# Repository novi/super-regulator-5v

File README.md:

# super-regulator-5v
Opamp-based super regulator (5V) schematic and PCB(KiCad format).

Negative voltage version is [here](https://github.com/novi/super-regulator-5v/tree/negative-voltage-version).

## Suitable parts

* TBD

## Acknowledgments

* [Op-Amp Based Linear Regulators](https://tangentsoft.net/elec/opamp-linreg.html)
* [The Superregs](https://linearaudio.nl/superregs)

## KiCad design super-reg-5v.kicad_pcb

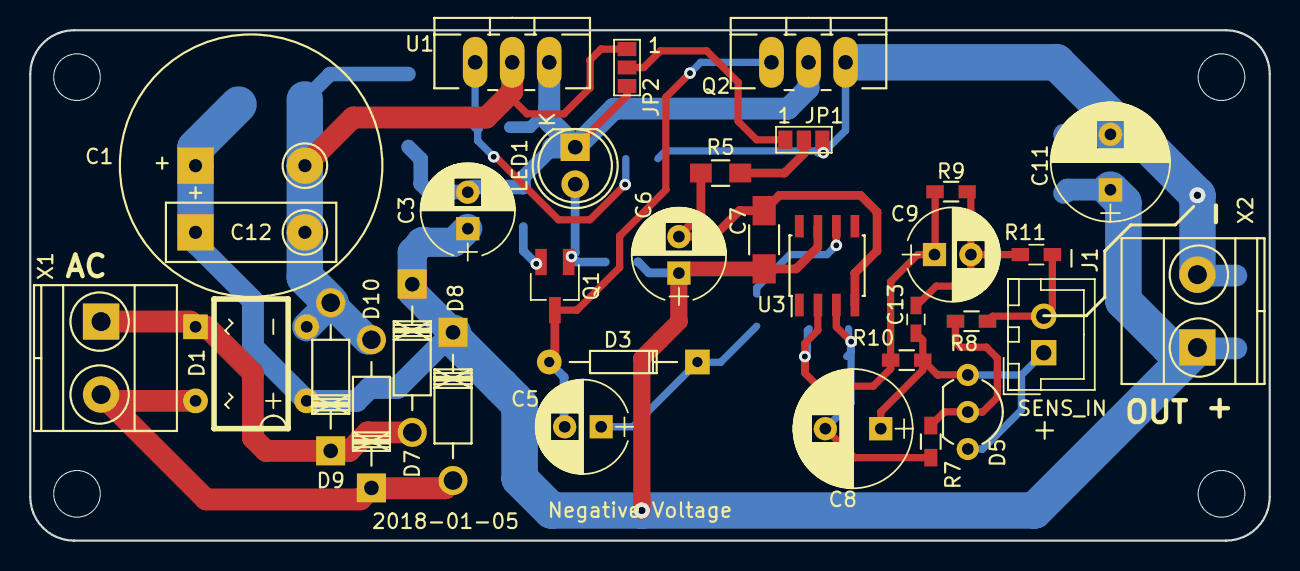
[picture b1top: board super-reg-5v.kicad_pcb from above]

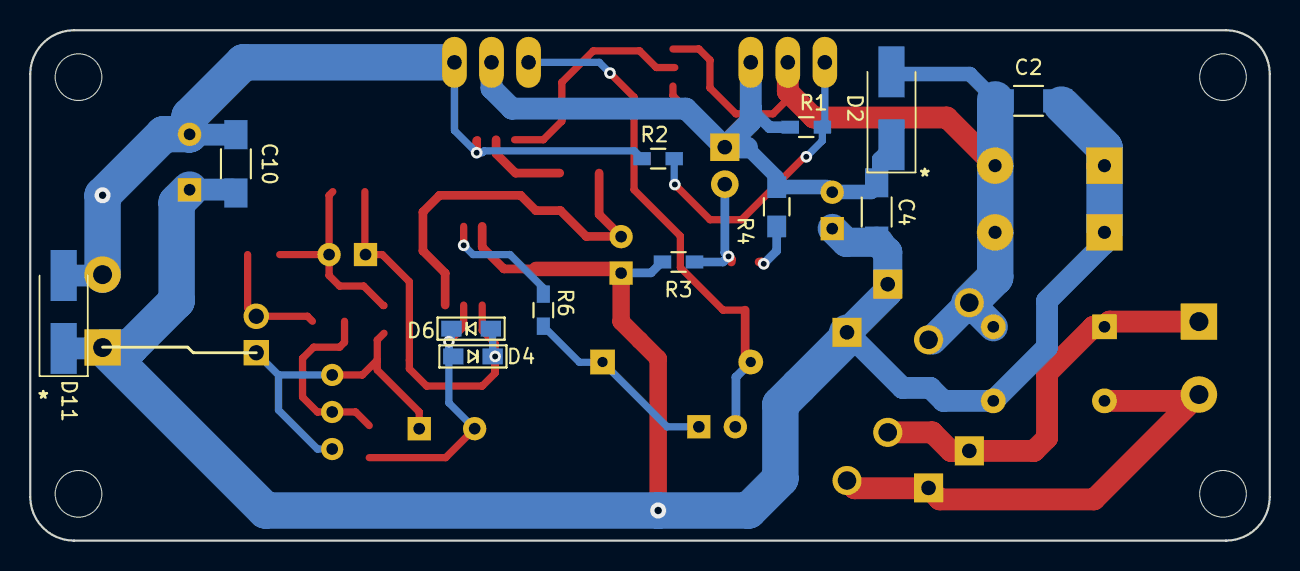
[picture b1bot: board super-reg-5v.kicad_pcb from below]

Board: 2 copper layers, 85.0 x 35.0 mm, 45 parts (12 on the bottom side), 21 nets.

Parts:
C1: 2200u; C_Radial_D18_L36_P7.5_LargePad
C2, C4, C7, C10: 0.1u C0G; C_1206_HandSoldering
C3, C6: 100u 35v LowESR; CP_Radial_D6.3mm_P2.50mm
C5: 100u LowESR; CP_Radial_D6.3mm_P2.50mm
C8: 100u EP-Cap; CP_Radial_D8.0mm_P3.80mm
C9: 100u; CP_Radial_D6.3mm_P2.50mm
C11: 220u OS-CON; CP_Radial_D8.0mm_P3.80mm
C12: C1-Alt; C_Radial_D18_L36_P7.5_LargePad_NoCircle
C13: 100p; C_0603_HandSoldering
D1: DB-1S(SDI2100); DB-1_DIP
D2, D11: D; D_SMA_Handsoldering
D3: ZD 2.7V; Diode_DO-35_SOD27_Horizontal_RM10
D4, D6: D; UMD2-handsoldering
D5: TL431LP; TO-92_Inline_Wide
D7, D8, D9, D10: PWR_D; Diode_DO-41_SOD81_Horizontal_RM10
J1: SENS_IN; JST_XH_B02B-XH-A_02x2.50mm_Straight
JP1: OPAMP_PWR_2; GS3
JP2: OPAMP_PWR_1; GS3
LED1: LED GREEN(2V); LED-5MM
Q1: 2SC2712GR; SC-59_Handsoldering
Q2: D45H11; TO-220_Neutral123_Vertical_LargePads
R1, R9, R10: 1k 1%; R_0603_HandSoldering
R2: 820 1%; R_0603_HandSoldering
R3: 10k; R_0603_HandSoldering
R4: 240; R_0805_HandSoldering
R5: 100; R_0805_HandSoldering
R6: 10; R_0603_HandSoldering
R7: 470; R_0603_HandSoldering
R8: 2.2k; R_0603_HandSoldering
R11: 100; R_0603_HandSoldering
U1: LM337T; TO-220_Neutral123_Vertical_LargePads
U3: AD825; SOIC-8_3.9x4.9mm_Pitch1.27mm
X1: AC_IN; TerminalBlock_Pheonix_MKDS1.5-2pol
X2: DC_OUT; TerminalBlock_Pheonix_MKDS1.5-2pol

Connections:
/OPAMP_N: C9.1, D4.1, D6.2, R9.2, R10.1, U3.2
unnamed: C1.1, C2.2, C3.1, C4.2, C6.1, C7.2, C10.2, C11.1, C12.1, D1.3, D7.1, D8.1, D11.1, R3.2, U3.7, X2.1
unnamed: C1.2, C2.1, C12.2, D1.4, D2.2, D9.2, D10.2, JP2.1, U1.2
unnamed: C3.2, C4.1, D2.1, JP2.3, LED1.1, Q2.2, R1.1, R4.1, U1.3
unnamed: C5.1, D3.1, R6.2
unnamed: C5.2, D3.2, Q1.3, Q2.1
unnamed: C6.2, C7.1, R5.1, U3.4
unnamed: C8.2, D4.2, D6.1, R7.2, U3.3
unnamed: C10.1, C11.2, D11.2, JP1.3, Q2.3, R2.1, X2.2
unnamed: C8.1, C13.1, D5.1, D5.3, J1.1, R10.2
unnamed: C9.2, C13.2, R9.1, R11.1
unnamed: D1.1, D7.2, D9.1, X1.1
unnamed: D1.2, D8.2, D10.1, X1.2
unnamed: D5.2, R7.1, R8.1
unnamed: J1.2, R8.2, R11.2
unnamed: JP1.1, JP2.2
unnamed: JP1.2, R5.2
unnamed: LED1.2, Q1.1, R3.1
unnamed: Q1.2, R4.2
unnamed: R1.2, R2.2, U1.1
unnamed: R6.1, U3.6

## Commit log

2016-07-25 Add KiCad project (schematic and PCB)
2016-07-26 change generic diode package to TUMD2 larger capacitor pad
2016-07-26 larger via pad size change silk for bridge-diode D1
2016-07-27 minor track fix
2016-07-31 Add AC silk and dates
2016-08-20 change recommended parts
2016-08-28 change footprint for the diode add an alternate op-amp footprint
2016-08-28 change the date on the board
2016-09-27 change PCB size (35mm x 85mm) add alternate C1
2016-09-28 add alternate bridge diode
2016-10-20 change the alternate bridge-D to single bridge diodes
2016-11-04 update PCB
2016-11-04 change bypass Cap
2017-01-10 fix track width
2017-01-10 minor fix
2017-05-17 migrate library
2017-05-17 update components
2017-05-17 fix library error
2017-05-18 update footprints
2017-09-09 separate sensor input refactor components
2017-12-16 fix track add sensor line silk minor fix
2017-12-17 add masks fix silks
2017-12-25 update transistor package changes for opams power
2017-12-25 for negative voltage
2017-12-25 update plot path
2018-01-05 fix sens silk
2021-05-26 update values
